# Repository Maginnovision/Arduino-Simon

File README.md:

# Arduino-Simon

Arduino SW is the arduino sketch for the simon game. The sketch is written for the custom board with arduino/genuino micro bootloader. The required software I2C and display libraries are included for the following reason. As of the first board revision there was no plan to have a display so I2C lines were used for buttons. To add the display and use 4 analog pins for it required the software I2C library. The display library of course needed some modification to work with this as well.

Eagle HW has the Eagle board and schematic files. Also included are PDF versions of both files viewable from a browser. The display used is a .96" ssd1306 I2C OLED display found places like adafruit, amazon, and ebay. The arcade style light up buttons were bought from addicore.com. Will add schematics for the amplifier "soon". It is just an LM386 based amplifier with a logarithmic pot and a voltage divider on the input signal since they don't really want 5V input signal.

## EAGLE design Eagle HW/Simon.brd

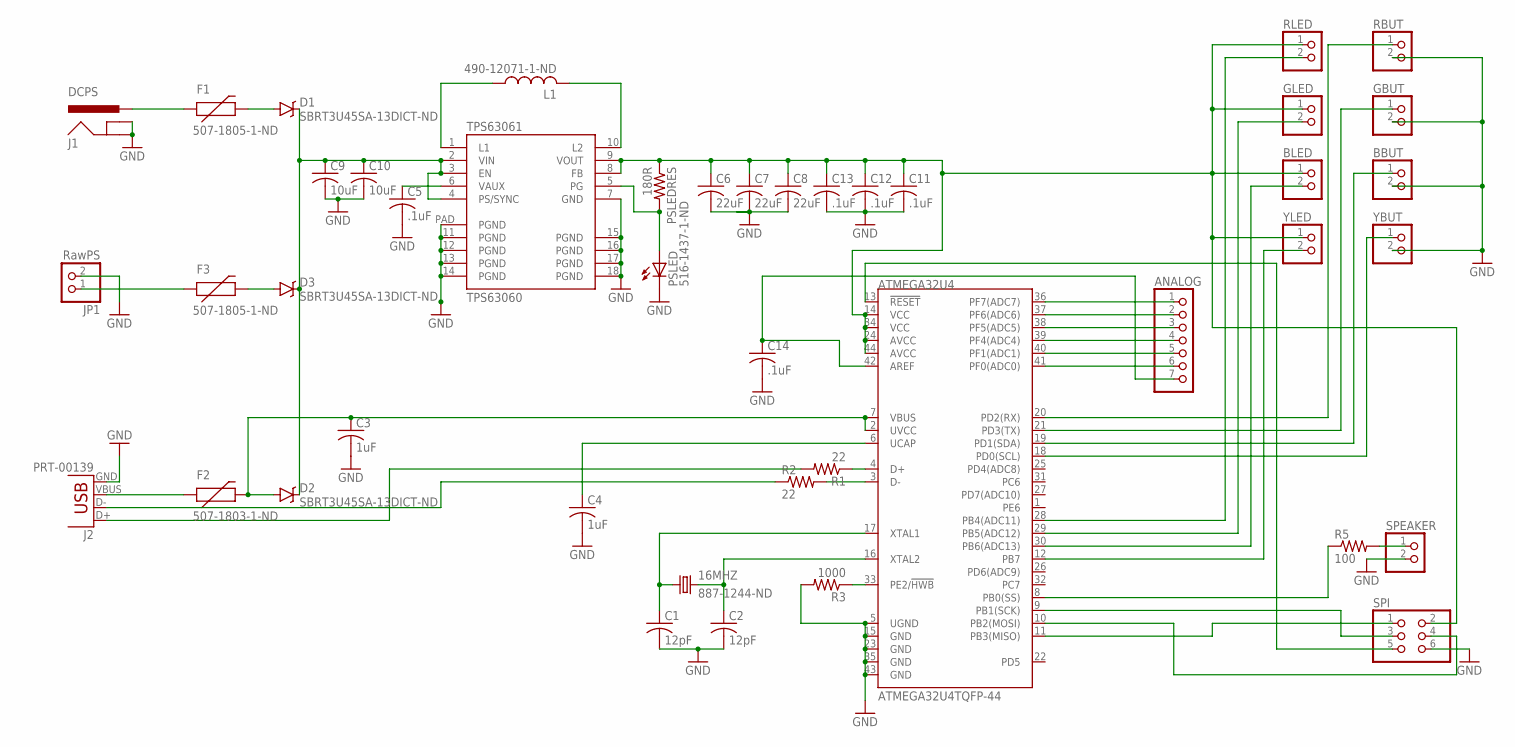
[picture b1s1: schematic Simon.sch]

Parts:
16MHZ: 887-1244-ND; HC49US
ANALOG: PINHD-1X7; 1X07
ATMEGA32U4: ATMEGA32U4TQFP-44; TQFP44
BBUT: PINHD-1X2; 1X02
BLED: PINHD-1X2; 1X02
C1, C2: 12pF; C0805
C3, C4: 1uF; C0805
C5, C11, C12, C13, C14: .1uF; C0805
C6, C7, C8: 22uF; C0805
C9, C10: 10uF; C0805
D1, D2, D3: SBRT3U45SA-13DICT-ND; SMA-DIODE
F1, F3: 507-1805-1-ND; PTC-1206-WIDE
F2: 507-1803-1-ND; PTC-1206-WIDE
GBUT: PINHD-1X2; 1X02
GLED: PINHD-1X2; 1X02
J1: DCPS; POWER_JACK_SMD
J2: PRT-00139; USB-B-PTH
JP1: RawPS; 1X02/90
L1: 490-12071-1-ND; L2012C
PSLED: 516-1437-1-ND; SML0805
PSLEDRES: 180R; R0805
R1, R2: 22; R0805
R3: 1000; R0805
R5: 100; R0805
RBUT: PINHD-1X2; 1X02
RLED: PINHD-1X2; 1X02
SPEAKER: PINHD-1X2; 1X02
SPI: PINHD-2X3; 2X03
TPS63061: TPS63060; QFN-10_PAD-8
YBUT: PINHD-1X2; 1X02
YLED: PINHD-1X2; 1X02

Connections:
5VREG: ATMEGA32U4.14 (VCC), ATMEGA32U4.24 (AVCC), ATMEGA32U4.34 (VCC), ATMEGA32U4.44 (AVCC), BLED.1, C6.1, C7.1, C8.1, C11.1, C12.1, C13.1, GLED.1, PSLEDRES.1, RLED.1, SPI.2, TPS63061.8 (FB), TPS63061.9 (VOUT), YLED.1
A0SIG: ANALOG.1, ATMEGA32U4.36 (PF7(ADC7))
A1SIG: ANALOG.2, ATMEGA32U4.37 (PF6(ADC6))
A2SIG: ANALOG.3, ATMEGA32U4.38 (PF5(ADC5))
A3SIG: ANALOG.4, ATMEGA32U4.39 (PF4(ADC4))
A4SIG: ANALOG.5, ATMEGA32U4.40 (PF1(ADC1))
A5SIG: ANALOG.6, ATMEGA32U4.41 (PF0(ADC0))
AREF: ANALOG.7, ATMEGA32U4.42 (AREF), C14.1
BBUTSIG: ATMEGA32U4.19 (PD1(SDA)), BBUT.1
BLEDSIG: ATMEGA32U4.30 (PB6(ADC13)), BLED.2
D_N: ATMEGA32U4.3 (D-), R2.2
D_P: ATMEGA32U4.4 (D+), R1.1
FUSED-DCIN: D1.A, F1.2
FUSED-RAWPS: D3.A, F3.2
FUSED-USBIN: ATMEGA32U4.2 (UVCC), ATMEGA32U4.7 (VBUS), C3.1, D2.A, F2.2
GBUTSIG: ATMEGA32U4.21 (PD3(TX)), GBUT.1
GLEDSIG: ATMEGA32U4.29 (PB5(ADC12)), GLED.2
GND: ATMEGA32U4.5 (UGND), ATMEGA32U4.15 (GND), ATMEGA32U4.23 (GND), ATMEGA32U4.35 (GND), ATMEGA32U4.43 (GND), BBUT.2, C1.2, C2.2, C3.2, C4.2, C5.2, C6.2, C7.2, C8.2, C9.2, C10.2, C11.2, C12.2, C13.2, C14.2, GBUT.2, J1.GND (GNDBREAK), J1.P$4 (GND), J2.GND, JP1.2, PSLED.C, R3.2, RBUT.2, SPEAKER.2, SPI.6, TPS63061.7 (GND), TPS63061.11 (PGND), TPS63061.12 (PGND), TPS63061.13 (PGND), TPS63061.14 (PGND), TPS63061.15 (PGND), TPS63061.16 (PGND), TPS63061.17 (PGND), TPS63061.18 (PGND), TPS63061.PAD (PGND), YBUT.2
HWB: ATMEGA32U4.33 (PE2/!HWB), R3.1
IND1: L1.1, TPS63061.1 (L1)
IND2: L1.2, TPS63061.10 (L2)
MISO: ATMEGA32U4.11 (PB3(MISO)), SPI.1
MOSI: ATMEGA32U4.10 (PB2(MOSI)), SPI.4
PGSIGNAL: PSLED.A, PSLEDRES.2, TPS63061.5 (PG)
PSCAP: C5.1, TPS63061.6 (VAUX)
PSIN: C9.1, C10.1, D1.C, D2.C, D3.C, TPS63061.2 (VIN), TPS63061.3 (EN), TPS63061.4 (PS/SYNC)
RAW-DC: F1.1, J1.VIN0 (PWR)
RAW-PS: F3.1, JP1.1
RAW-USB_N: J2.D-, R2.1
RAW-USB_P: J2.D+, R1.2
RAW-VUSB: F2.1, J2.VBUS
RBUTSIG: ATMEGA32U4.20 (PD2(RX)), RBUT.1
RESET: ATMEGA32U4.13 (!RESET), SPI.5
RLEDSIG: ATMEGA32U4.28 (PB4(ADC11)), RLED.2
SPEAKERPORT: ATMEGA32U4.8 (PB0(SS)), R5.1
SPEAKERSUPPLY: R5.2, SPEAKER.1
SPICLOCK: ATMEGA32U4.9 (PB1(SCK)), SPI.3
UCAP: ATMEGA32U4.6 (UCAP), C4.1
XTAL1: 16MHZ.1, ATMEGA32U4.17 (XTAL1), C1.1
XTAL2: 16MHZ.2, ATMEGA32U4.16 (XTAL2), C2.1
YBUTSIG: ATMEGA32U4.18 (PD0(SCL)), YBUT.1
YLEDSIG: ATMEGA32U4.12 (PB7), YLED.2

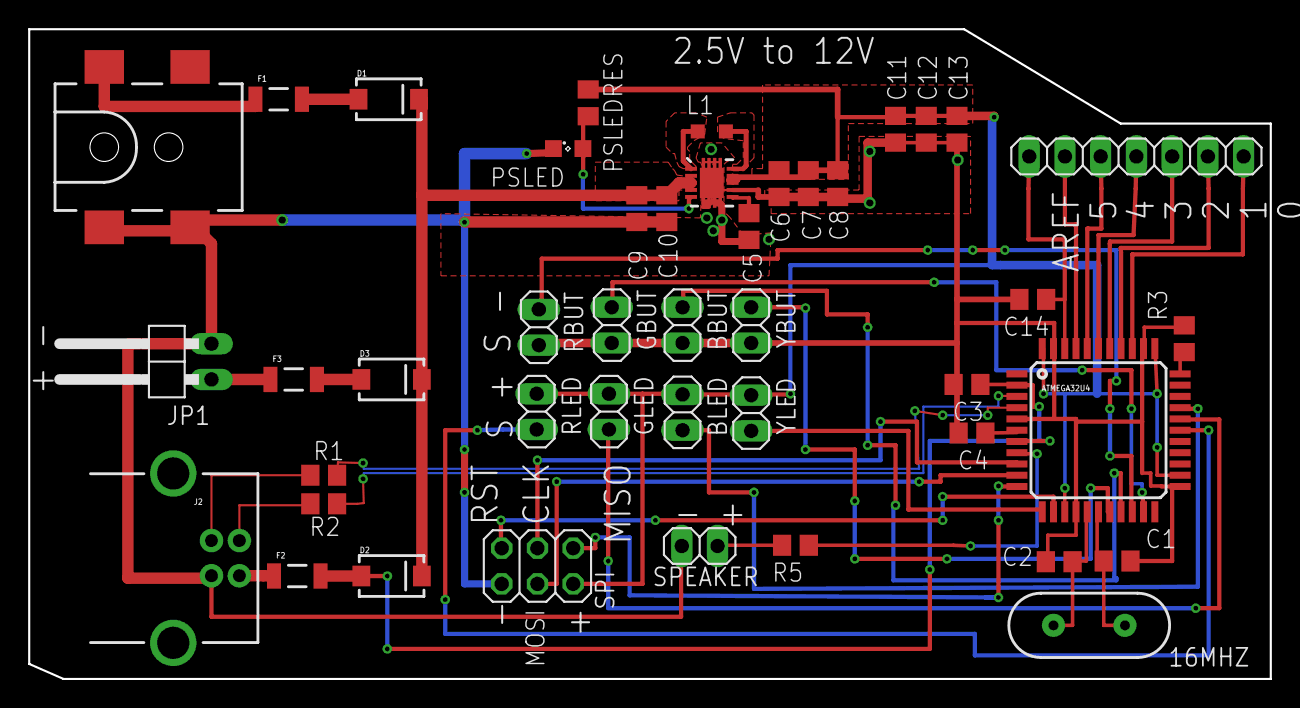
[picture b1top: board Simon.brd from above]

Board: 2 copper layers, 88.2 x 46.2 mm, 44 parts (0 on the bottom side), 42 nets.

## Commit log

2016-12-23 :tada: Added .gitattributes & .gitignore files
2016-12-23 Initial Commit
    Added arduino sketch for simon game.
    Added eagle hardware files and PDF versions of same files.
2016-12-23 Added README
    Added a readme to root directory, also rename simon schematic pdf to
    have the same format as board.
2016-12-23 Small change to PDF
2016-12-24 Made changes to improve debouncing
    New arcade style buttons do not function as the old ones did and the
    debouncing had to be made extra aggressive. Should be fixed now, even if
    mildly unresponsive.
2016-12-25 Sleep and debounce updates
    Forced 100ms light/sound on press detection. Added a #define for number
    of rounds. Updated sleep to turn off lights and speaker first. Fixed
    duration of red_sound tone for game over.
2017-01-02 Added 128x64 OLED display
    To keep program all inclusive included all files for displays instead of
    library dependencies. Part of the reason is the required changes to the
    libraries to make them work properly. Uses a software I2C library which
    was modified so that the creation could be managed at compile time, not
    run time. The adafruit display library was modified to use the software
    wire library, and accept which pins are being used for software I2C
2017-01-02 Modified to make smaller, add high score
    Minimized code size for both GFX and SSD1306. Both and SoftwareWire
    modified to be more suited to program. Also re-formatted all source
    files with auto formatter. Added high score support to program which
    uses eeprom byte 0.
2017-01-14 High score/display changes
    Added high score code to its own function. Fixed display output so
    scores always fit on single line. Changed random seed to only use analog
    pins 4 and 5 since display is connected to 0-3. Added high score reset
    by holding all 4 buttons while resetting.

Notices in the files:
parts and their libraries:
SparkFun-PowerIC: Licensing: Creative Commons ShareAlike 4.0 International - https://creativecommons.org/licenses/by-sa/4.0
